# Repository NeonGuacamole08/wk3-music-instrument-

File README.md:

# TouchedOutSythn

For this, I followed the GuitarML YouTube video https://www.youtube.com/watch?v=tRJoIYXkm-U&t=23s and guide https://github.com/GuitarML/TouchedOutSynth
## The Schematics:

 For this, you will need:
 Electrosmith_Daisy_Seed_Rev4 as your microcontroller 
 2 Adafruit MPR121 Breakout boards that I downloaded from https://www.snapeda.com/parts/1982/Adafruit+Industries/view-part/?ref=snap 
 2 AudioJack3 
 and a Barrel_Jack_Switch. For the wiring of these, please follow the images below :

Use "A" to choose symbols like the microcontrollers 
Use "P" for power symbols like GND or 3.3V
Use "L" to label portions

 ### The microcontroller 

 ### The Touch Pad 

### Key Pads 

### Audio Jacks 

### Sliders 

### Potential Meters Valley

## The PCB

Make sure to route all the blue lines. 
Design the shape of your PCB using edge cuts

To insert a drawing as I did, 
Click on Image Converter in KiCad

From there, you will end up here:

From the file menu, upload the image that you want to use (Make sure to use an image that has a lot of contrast) 
Now, since we are putting our designs on the PCB, select 

and export to clipboard. You can then go back to your PCB and press CTRL+V to paste your image. 

We are done!!!!

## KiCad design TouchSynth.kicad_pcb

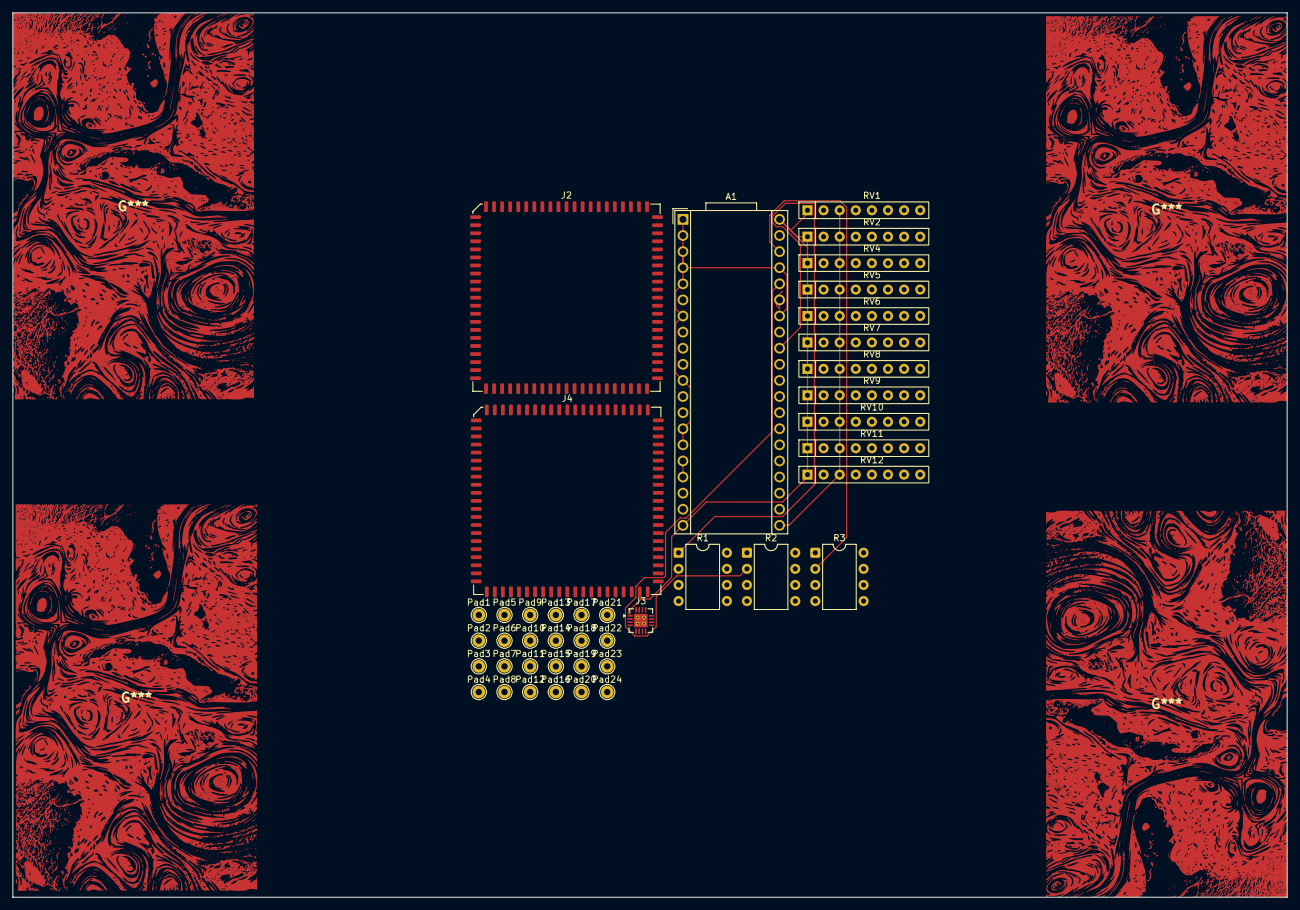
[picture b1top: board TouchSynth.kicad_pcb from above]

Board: 2 copper layers, 201.0 x 139.5 mm, 42 parts (0 on the bottom side), 14 nets.

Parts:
A1: Electrosmith_Daisy_Seed_Rev4; Electrosmith_Daisy_Seed
J2, J4: AudioJack3; PLCC-84_29.3x29.3mm_P1.27mm
J3: Barrel_Jack_Switch; Texas_RVA_VQFN-16-1EP_3.5x3.5mm_P0.5mm_EP2.14x2.14mm_Therma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
Pad1, Pad2, Pad3, Pad4, Pad5, Pad6, Pad7, Pad8, Pad9, Pad10, Pad11, Pad12, Pad13, Pad14, Pad15, Pad16, Pad17, Pad18, Pad19, Pad20, Pad21, Pad22, Pad23, Pad24: TestPoint_THTPad_D2.0mm_Drill1.0mm
R1, R2, R3: R; DIP-8_W7.62mm
RV1, RV2: R_Potentiometer_Trim_US; R_Array_SIP8
RV4, RV5, RV6, RV7, RV8, RV9, RV10, RV11, RV12: 10k; R_Array_SIP8

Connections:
+3.3V: A1.38 (3V3_D), R3.2
+3.3VA: A1.21 (3V3_A), RV1.3, RV2.3, RV4.3, RV5.3, RV6.3, RV7.3, RV8.3, RV9.3, RV10.3, RV11.3, RV12.3
/x: A1.1 (USB_ID), A1.2 (SD_DATA_3), A1.3 (SD_DATA_2), A1.4 (SD_DATA_1), A1.5 (SD_DATA_0), A1.7 (SD_CLK), A1.11 (SPI1_PICO), A1.14 (USART1_TX), A1.15 (USART1_RX), A1.16 (AUDIO_IN_1), A1.17 (AUDIO_IN_2), A1.33 (SAI2_SD_A), A1.34 (SAI2_FS), A1.37 (USB_D_+)
GND: A1.20 (AGND), A1.40 (DGND), J3.1, J3.3, RV1.1, RV2.1, RV4.1, RV5.1, RV6.1, RV7.1, RV8.1, RV9.1, RV10.1, RV11.1, RV12.1
JOYSTICK_Y: A1.32 (SAI2_SD_B), R1.1
MIDI_OUT: A1.36 (USB_D_-), R2.2
POT_1: A1.22 (ADC_0), RV6.2
POT_3: A1.24 (ADC_2), RV9.2
POT_4: A1.25 (ADC_3), RV11.2
POT_5: A1.35 (SAI2_SCK), RV4.2, RV10.2
SLIDE_POT1: A1.26 (ADC_4), RV7.2
SLIDE_POT2: A1.27 (ADC_5), RV5.2
SLIDE_POT3: A1.28 (ADC_6), RV8.2
SLIDE_POT4: A1.29 (DAC_OUT2), RV12.2
